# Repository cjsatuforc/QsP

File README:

3D Printer main driver board incorporating Atmel XMEGA. Inspired by RUMBA and other RepRap projects.

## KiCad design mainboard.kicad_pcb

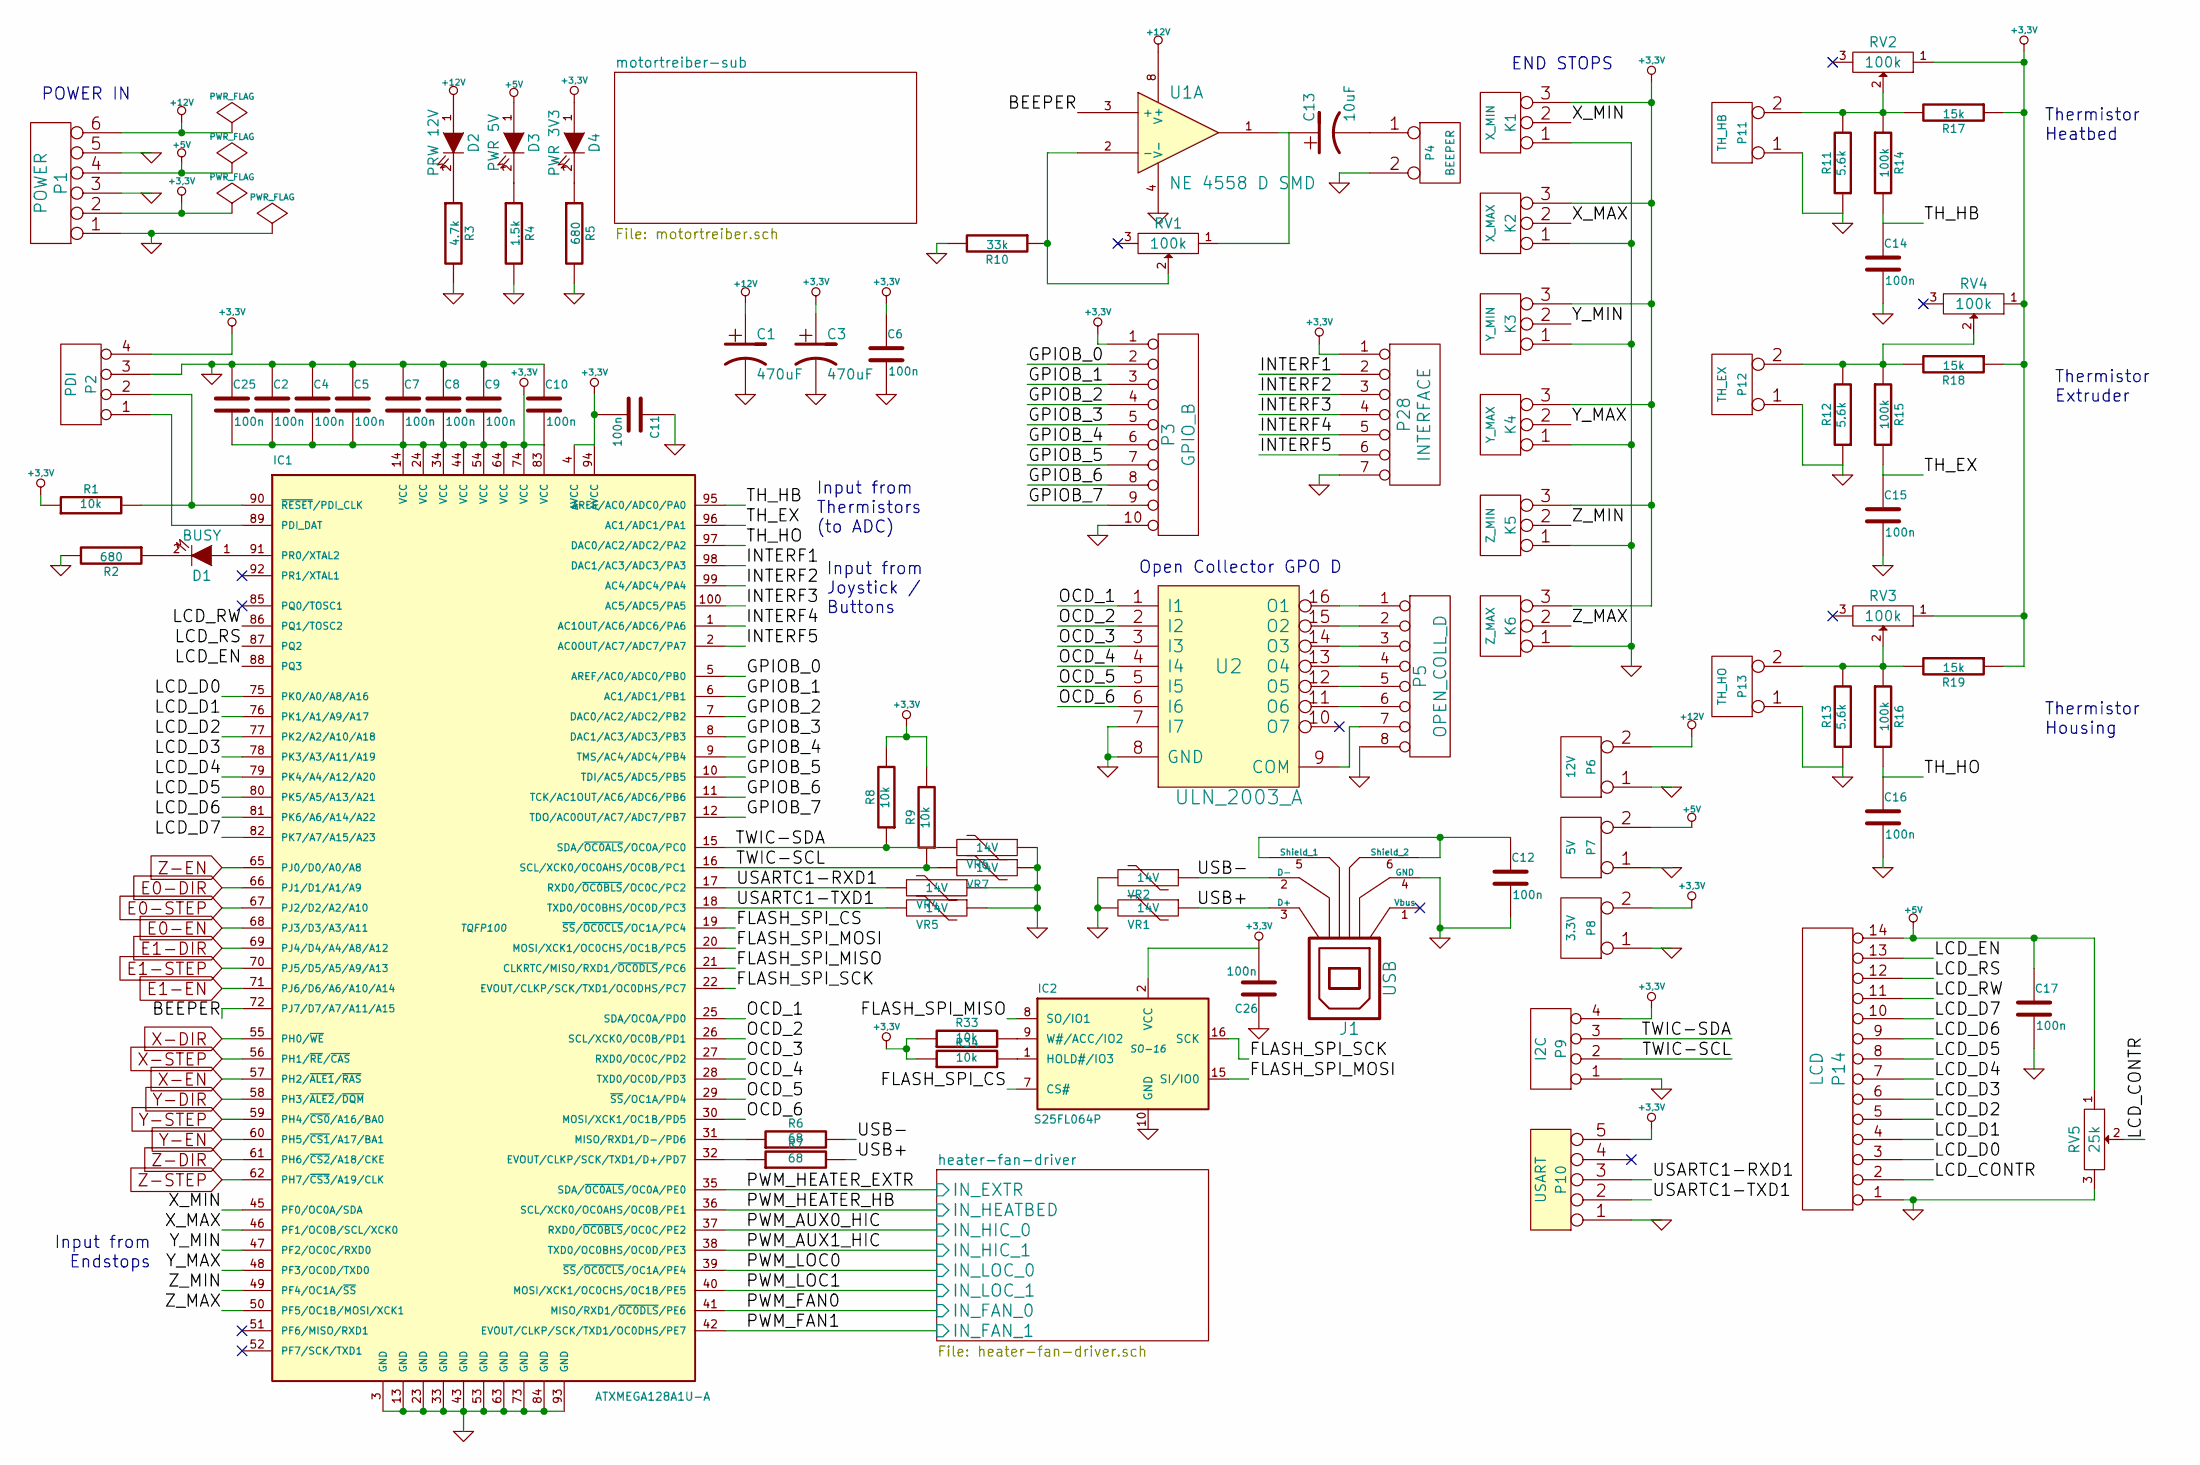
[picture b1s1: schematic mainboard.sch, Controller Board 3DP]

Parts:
C1, C3: 470uF
C2, C4, C5, C6, C7, C8, C9, C10, C11, C25, C26: 100n
C12, C14, C15, C16, C17: 100n
C13: 10uF
D1: BUSY
D2: PRW 12V
D3: PWR 5V
D4: PWR 3V3
IC1: ATXMEGA128A1U-A; TQFP100
IC2: S25FL064P; SO-16
J1: USB
K1: X_MIN
K2: X_MAX
K3: Y_MIN
K4: Y_MAX
K5: Z_MIN
K6: Z_MAX
P1: POWER
P2: PDI
P3: GPIO_B
P4: BEEPER
P5: OPEN_COLL_D
P6: 12V
P7: 5V
P8: 3.3V
P9: I2C
P10: USART
P11: TH_HB
P12: TH_EX
P13: TH_HO
P14: LCD
P28: INTERFACE
R1: 10k
R2, R5: 680
R3: 4.7k
R4: 1.5k
R6, R7: 68
R8, R9, R33, R34: 10k
R10: 33k
R11, R12, R13: 5.6k
R14, R15, R16: 100k
R17, R18, R19: 15k
RV1, RV2, RV3, RV4: 100k
RV5: 25k
U1: NE 4558 D SMD
U2: ULN_2003_A
VR1, VR2, VR4, VR5, VR6, VR7: 14V

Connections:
+3.3V: C2.2, C3.1, C4.2, C5.2, C6.1, C7.2, C8.2, C9.2, C10.2, C11.2, C25.2, C26.2, D4.1 (A), IC1.4 (AVCC), IC1.14 (VCC), IC1.24 (VCC), IC1.34 (VCC), IC1.44 (VCC), IC1.54 (VCC), IC1.64 (VCC), IC1.74 (VCC), IC1.83 (VCC), IC1.94 (AVCC), IC2.2 (VCC), K1.3, K2.3, K3.3, K4.3, K5.3, K6.3, P1.2, P2.4, P3.1, P8.2 (PM), P9.4, P10.5, P28.1, R1.1, R8.2, R9.2, R17.1, R18.1, R19.1, R33.1, R34.1, RV2.1, RV3.1, RV4.1; also elsewhere on the board
+5V: C17.1, D3.1 (A), P1.4, P7.2 (PM), P14.14, RV5.1
+12V: C1.1, D2.1 (A), P1.6, P6.2 (PM), U1.8 (V+); also elsewhere on the board
/BEEPER: IC1.72 (PJ7/D7/A7/A11/A15), U1.3 (+)
/FLASH_SPI_CS: IC1.19 (~SS~/~OC0CLS~/OC1A/PC4), IC2.7 (CS#)
/FLASH_SPI_MISO: IC1.21 (CLKRTC/MISO/RXD1/~OC0DLS~/PC6), IC2.8 (SO/IO1)
/FLASH_SPI_MOSI: IC1.20 (MOSI/XCK1/OC0CHS/OC1B/PC5), IC2.15 (SI/IO0)
/FLASH_SPI_SCK: IC1.22 (EVOUT/CLKP/SCK/TXD1/OC0DHS/PC7), IC2.16 (SCK)
/GPIOB_0: IC1.5 (AREF/AC0/ADC0/PB0), P3.2
/GPIOB_1: IC1.6 (AC1/ADC1/PB1), P3.3
/GPIOB_2: IC1.7 (DAC0/AC2/ADC2/PB2), P3.4
/GPIOB_3: IC1.8 (DAC1/AC3/ADC3/PB3), P3.5
/GPIOB_4: IC1.9 (TMS/AC4/ADC4/PB4), P3.6
/GPIOB_5: IC1.10 (TDI/AC5/ADC5/PB5), P3.7
/GPIOB_6: IC1.11 (TCK/AC1OUT/AC6/ADC6/PB6), P3.8
/GPIOB_7: IC1.12 (TDO/AC0OUT/AC7/ADC7/PB7), P3.9
/INTERF1: IC1.98 (DAC1/AC3/ADC3/PA3), P28.2
/INTERF2: IC1.99 (AC4/ADC4/PA4), P28.3
/INTERF3: IC1.100 (AC5/ADC5/PA5), P28.4
/INTERF4: IC1.1 (AC1OUT/AC6/ADC6/PA6), P28.5
/INTERF5: IC1.2 (AC0OUT/AC7/ADC7/PA7), P28.6
/LCD_CONTR: P14.2, RV5.2
/LCD_D0: IC1.75 (PK0/A0/A8/A16), P14.3
/LCD_D1: IC1.76 (PK1/A1/A9/A17), P14.4
/LCD_D2: IC1.77 (PK2/A2/A10/A18), P14.5
/LCD_D3: IC1.78 (PK3/A3/A11/A19), P14.6
/LCD_D4: IC1.79 (PK4/A4/A12/A20), P14.7
/LCD_D5: IC1.80 (PK5/A5/A13/A21), P14.8
/LCD_D6: IC1.81 (PK6/A6/A14/A22), P14.9
/LCD_D7: IC1.82 (PK7/A7/A15/A23), P14.10
/LCD_EN: IC1.88 (PQ3), P14.13
/LCD_RS: IC1.87 (PQ2), P14.12
/LCD_RW: IC1.86 (PQ1/TOSC2), P14.11
/OCD_1: IC1.25 (SDA/OC0A/PD0), U2.1 (I1)
/OCD_2: IC1.26 (SCL/XCK0/OC0B/PD1), U2.2 (I2)
/OCD_3: IC1.27 (RXD0/OC0C/PD2), U2.3 (I3)
/OCD_4: IC1.28 (TXD0/OC0D/PD3), U2.4 (I4)
/OCD_5: IC1.29 (~SS~/OC1A/PD4), U2.5 (I5)
/OCD_6: IC1.30 (MOSI/XCK1/OC1B/PD5), U2.6 (I6)
/TH_EX: C15.1, IC1.96 (AC1/ADC1/PA1), R15.2
/TH_HB: C14.1, IC1.95 (AREF/AC0/ADC0/PA0), R14.2
/TH_HO: C16.1, IC1.97 (DAC0/AC2/ADC2/PA2), R16.2
/TWIC-SCL: IC1.16 (SCL/XCK0/OC0AHS/OC0B/PC1), P9.2, R9.1, VR7.2
/TWIC-SDA: IC1.15 (SDA/~OC0ALS~/OC0A/PC0), P9.3, R8.1, VR6.2
/USARTC1-RXD1: IC1.17 (RXD0/~OC0BLS~/OC0C/PC2), P10.3, VR4.2
/USARTC1-TXD1: IC1.18 (TXD0/OC0BHS/OC0D/PC3), P10.2, VR5.2
/USB+: J1.3 (D+), R7.2, VR1.1
/USB-: J1.2 (D-), R6.2, VR2.1
/X_MAX: IC1.46 (PF1/OC0B/SCL/XCK0), K2.2 (PM)
/X_MIN: IC1.45 (PF0/OC0A/SDA), K1.2 (PM)
/Y_MAX: IC1.48 (PF3/OC0D/TXD0), K4.2 (PM)
/Y_MIN: IC1.47 (PF2/OC0C/RXD0), K3.2 (PM)
/Z_MAX: IC1.50 (PF5/OC1B/MOSI/XCK1), K6.2 (PM)
/Z_MIN: IC1.49 (PF4/OC1A/~SS~), K5.2 (PM)
/heater-fan-driver/IN_EXTR: IC1.35 (SDA/~OC0ALS~/OC0A/PE0); also elsewhere on the board
/heater-fan-driver/IN_FAN_0: IC1.41 (MISO/RXD1/~OC0DLS~/PE6); also elsewhere on the board
/heater-fan-driver/IN_FAN_1: IC1.42 (EVOUT/CLKP/SCK/TXD1/OC0DHS/PE7); also elsewhere on the board
/heater-fan-driver/IN_HEATBED: IC1.36 (SCL/XCK0/OC0AHS/OC0B/PE1); also elsewhere on the board
/heater-fan-driver/IN_HIC_0: IC1.37 (RXD0/~OC0BLS~/OC0C/PE2); also elsewhere on the board
/heater-fan-driver/IN_HIC_1: IC1.38 (TXD0/OC0BHS/OC0D/PE3); also elsewhere on the board
/heater-fan-driver/IN_LOC_0: IC1.39 (~SS~/~OC0CLS~/OC1A/PE4); also elsewhere on the board
/heater-fan-driver/IN_LOC_1: IC1.40 (MOSI/XCK1/OC0CHS/OC1B/PE5); also elsewhere on the board
E0-DIR: IC1.66 (PJ1/D1/A1/A9); also elsewhere on the board
E0-EN: IC1.68 (PJ3/D3/A3/A11); also elsewhere on the board
E0-STEP: IC1.67 (PJ2/D2/A2/A10); also elsewhere on the board
E1-DIR: IC1.69 (PJ4/D4/A4/A8/A12); also elsewhere on the board
E1-EN: IC1.71 (PJ6/D6/A6/A10/A14); also elsewhere on the board
E1-STEP: IC1.70 (PJ5/D5/A5/A9/A13); also elsewhere on the board
GND: C1.2, C2.1, C3.2, C4.1, C5.1, C6.2, C7.1, C8.1, C9.1, C10.1, C11.1, C12.2, C14.2, C15.2, C16.2, C17.2, C25.1, C26.1, IC1.3 (GND), IC1.13 (GND), IC1.23 (GND), IC1.33 (GND), IC1.43 (GND), IC1.53 (GND), IC1.63 (GND), IC1.73 (GND), IC1.84 (GND), IC1.93 (GND), IC2.10 (GND), J1.4 (GND), K1.1, K2.1, K3.1, K4.1, K5.1, K6.1, P1.1, P1.3, P1.5, P2.3, P3.10, P4.2 (PM), P5.8, P6.1, P7.1, P8.1, P9.1, P10.1, P11.1, P12.1, P13.1, P14.1, P28.7, R2.2, R3.2, R4.2, R5.2, R10.2, R11.1, R12.1, R13.1, RV5.3, U1.4 (V-), U2.7 (I7), U2.8 (GND), VR1.2, VR2.2, VR4.1, VR5.1, VR6.1, VR7.1; also elsewhere on the board
unnamed: C12.1, J1.5 (Shield_1), J1.6 (Shield_2)
unnamed: C13.1, RV1.1, U1.1
unnamed: C13.2, P4.1
unnamed: D1.1 (A), IC1.91 (PR0/XTAL2)
unnamed: D1.2 (K), R2.1
unnamed: D2.2 (K), R3.1
unnamed: D3.2 (K), R4.1
unnamed: D4.2 (K), R5.1
unnamed: IC1.31 (MISO/RXD1/D-/PD6), R6.1
unnamed: IC1.32 (EVOUT/CLKP/SCK/TXD1/D+/PD7), R7.1
unnamed: IC1.89 (PDI_DAT), P2.1
unnamed: IC1.90 (~RESET~/PDI_CLK), P2.2, R1.2
unnamed: IC2.1 (HOLD#/IO3), R34.2
unnamed: IC2.9 (W#/ACC/IO2), R33.2
unnamed: P5.1, U2.16 (O1)
unnamed: P5.2, U2.15 (O2)
unnamed: P5.3, U2.14 (O3)
unnamed: P5.4, U2.13 (O4)
unnamed: P5.5, U2.12 (O5)
unnamed: P5.6, U2.11 (O6)
unnamed: P5.7, U2.9 (COM)
unnamed: P11.2 (PM), R11.2, R14.1, R17.2, RV2.2
unnamed: P12.2 (PM), R12.2, R15.1, R18.2, RV4.2
unnamed: P13.2 (PM), R13.2, R16.1, R19.2, RV3.2
unnamed: R10.1, RV1.2, U1.2 (-)
X-DIR: IC1.55 (PH0/~WE); also elsewhere on the board
X-EN: IC1.57 (PH2/~ALE1~/~RAS~); also elsewhere on the board
X-STEP: IC1.56 (PH1/~RE~/~CAS~); also elsewhere on the board
Y-DIR: IC1.58 (PH3/~ALE2~/~DQM~); also elsewhere on the board
Y-EN: IC1.60 (PH5/~CS1~/A17/BA1); also elsewhere on the board
Y-STEP: IC1.59 (PH4/~CS0~/A16/BA0); also elsewhere on the board
Z-DIR: IC1.61 (PH6/~CS2~/A18/CKE); also elsewhere on the board
Z-EN: IC1.65 (PJ0/D0/A0/A8); also elsewhere on the board
Z-STEP: IC1.62 (PH7/~CS3~/A19/CLK); also elsewhere on the board

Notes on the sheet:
POWER IN
END STOPS
Thermistor Heatbed
Thermistor Extruder
Thermistor Housing
Input from Endstops
Input from Thermistors (to ADC)
Input from Joystick / Buttons
Open Collector GPO D

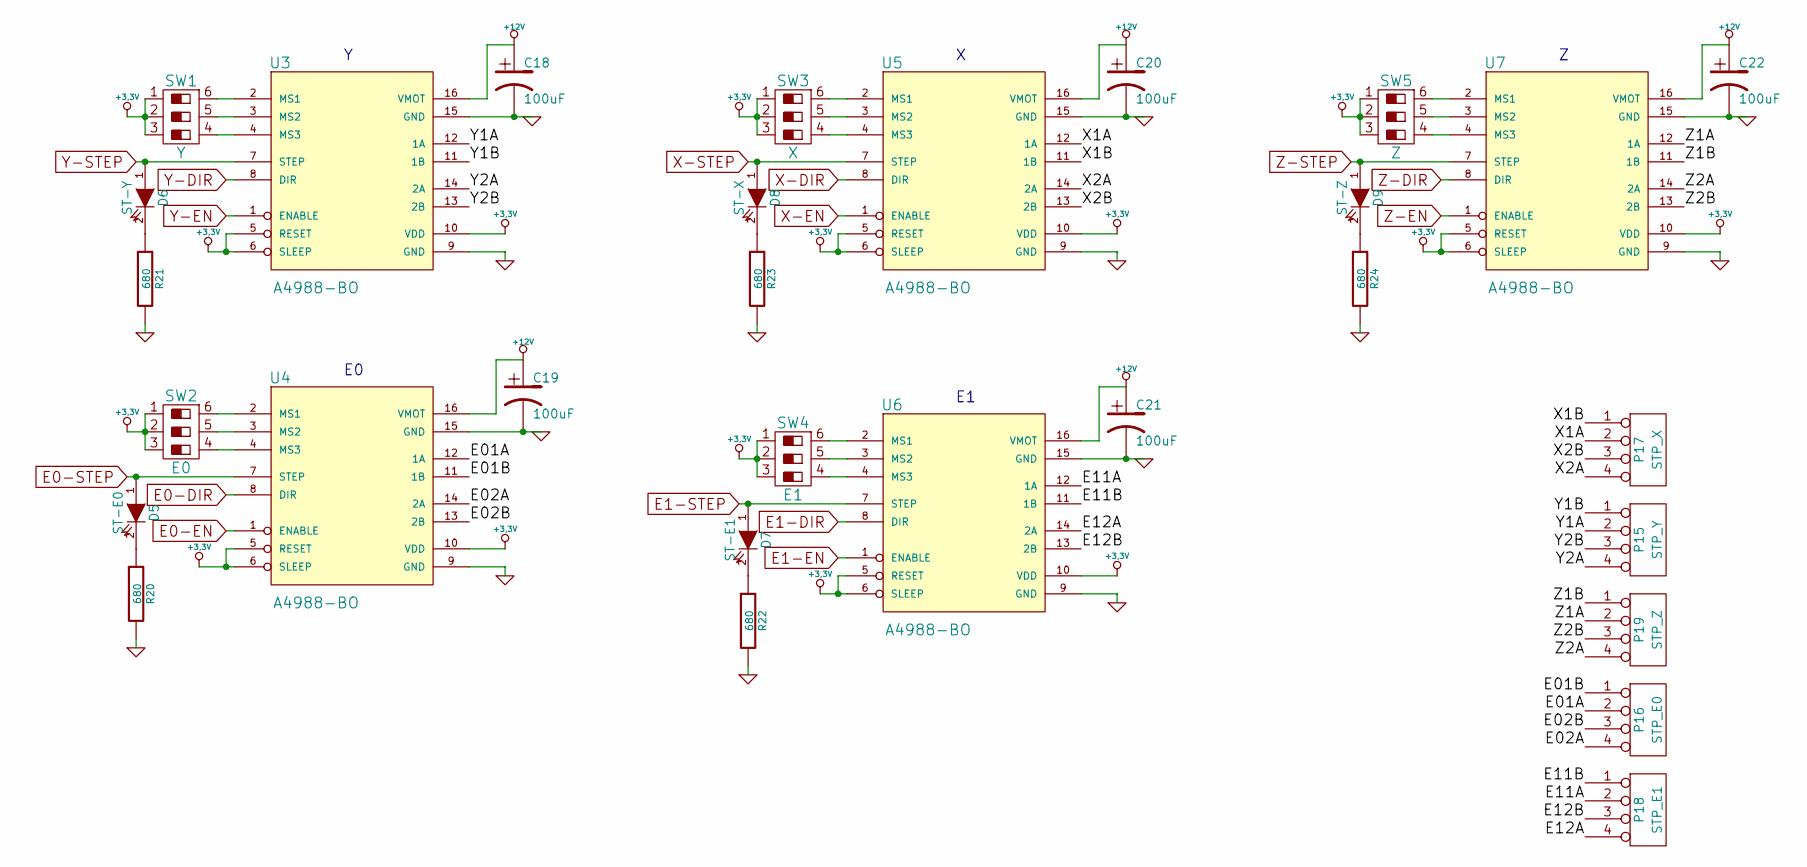
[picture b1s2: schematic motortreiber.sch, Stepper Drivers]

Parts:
C18, C19, C20, C21, C22: 100uF
D5: ST-E0
D6: ST-Y
D7: ST-E1
D8: ST-X
D9: ST-Z
P15: STP_Y
P16: STP_E0
P17: STP_X
P18: STP_E1
P19: STP_Z
R20, R21, R22, R23, R24: 680
SW1: Y
SW2: E0
SW3: X
SW4: E1
SW5: Z
U3, U4, U5, U6, U7: A4988-BO

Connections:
+3.3V: SW1.1, SW1.2, SW1.3, SW2.1, SW2.2, SW2.3, SW3.1, SW3.2, SW3.3, SW4.1, SW4.2, SW4.3, SW5.1, SW5.2, SW5.3, U3.5 (RESET), U3.6 (SLEEP), U3.10 (VDD), U4.5 (RESET), U4.6 (SLEEP), U4.10 (VDD), U5.5 (RESET), U5.6 (SLEEP), U5.10 (VDD), U6.5 (RESET), U6.6 (SLEEP), U6.10 (VDD), U7.5 (RESET), U7.6 (SLEEP), U7.10 (VDD); also elsewhere on the board
+12V: C18.1, C19.1, C20.1, C21.1, C22.1, U3.16 (VMOT), U4.16 (VMOT), U5.16 (VMOT), U6.16 (VMOT), U7.16 (VMOT); also elsewhere on the board
/motortreiber-sub/E01A: P16.2, U4.12 (1A)
/motortreiber-sub/E01B: P16.1, U4.11 (1B)
/motortreiber-sub/E02A: P16.4, U4.14 (2A)
/motortreiber-sub/E02B: P16.3, U4.13 (2B)
/motortreiber-sub/E11A: P18.2, U6.12 (1A)
/motortreiber-sub/E11B: P18.1, U6.11 (1B)
/motortreiber-sub/E12A: P18.4, U6.14 (2A)
/motortreiber-sub/E12B: P18.3, U6.13 (2B)
/motortreiber-sub/X1A: P17.2, U5.12 (1A)
/motortreiber-sub/X1B: P17.1, U5.11 (1B)
/motortreiber-sub/X2A: P17.4, U5.14 (2A)
/motortreiber-sub/X2B: P17.3, U5.13 (2B)
/motortreiber-sub/Y1A: P15.2, U3.12 (1A)
/motortreiber-sub/Y1B: P15.1, U3.11 (1B)
/motortreiber-sub/Y2A: P15.4, U3.14 (2A)
/motortreiber-sub/Y2B: P15.3, U3.13 (2B)
/motortreiber-sub/Z1A: P19.2, U7.12 (1A)
/motortreiber-sub/Z1B: P19.1, U7.11 (1B)
/motortreiber-sub/Z2A: P19.4, U7.14 (2A)
/motortreiber-sub/Z2B: P19.3, U7.13 (2B)
E0-DIR: U4.8 (DIR); also elsewhere on the board
E0-EN: U4.1 (ENABLE); also elsewhere on the board
E0-STEP: D5.1 (A), U4.7 (STEP); also elsewhere on the board
E1-DIR: U6.8 (DIR); also elsewhere on the board
E1-EN: U6.1 (ENABLE); also elsewhere on the board
E1-STEP: D7.1 (A), U6.7 (STEP); also elsewhere on the board
GND: C18.2, C19.2, C20.2, C21.2, C22.2, R20.2, R21.2, R22.2, R23.2, R24.2, U3.9 (GND), U3.15 (GND), U4.9 (GND), U4.15 (GND), U5.9 (GND), U5.15 (GND), U6.9 (GND), U6.15 (GND), U7.9 (GND), U7.15 (GND); also elsewhere on the board
unnamed: D5.2 (K), R20.1
unnamed: D6.2 (K), R21.1
unnamed: D7.2 (K), R22.1
unnamed: D8.2 (K), R23.1
unnamed: D9.2 (K), R24.1
unnamed: SW1.4, U3.4 (MS3)
unnamed: SW1.5, U3.3 (MS2)
unnamed: SW1.6, U3.2 (MS1)
unnamed: SW2.4, U4.4 (MS3)
unnamed: SW2.5, U4.3 (MS2)
unnamed: SW2.6, U4.2 (MS1)
unnamed: SW3.4, U5.4 (MS3)
unnamed: SW3.5, U5.3 (MS2)
unnamed: SW3.6, U5.2 (MS1)
unnamed: SW4.4, U6.4 (MS3)
unnamed: SW4.5, U6.3 (MS2)
unnamed: SW4.6, U6.2 (MS1)
unnamed: SW5.4, U7.4 (MS3)
unnamed: SW5.5, U7.3 (MS2)
unnamed: SW5.6, U7.2 (MS1)
X-DIR: U5.8 (DIR); also elsewhere on the board
X-EN: U5.1 (ENABLE); also elsewhere on the board
X-STEP: D8.1 (A), U5.7 (STEP); also elsewhere on the board
Y-DIR: U3.8 (DIR); also elsewhere on the board
Y-EN: U3.1 (ENABLE); also elsewhere on the board
Y-STEP: D6.1 (A), U3.7 (STEP); also elsewhere on the board
Z-DIR: U7.8 (DIR); also elsewhere on the board
Z-EN: U7.1 (ENABLE); also elsewhere on the board
Z-STEP: D9.1 (A), U7.7 (STEP); also elsewhere on the board

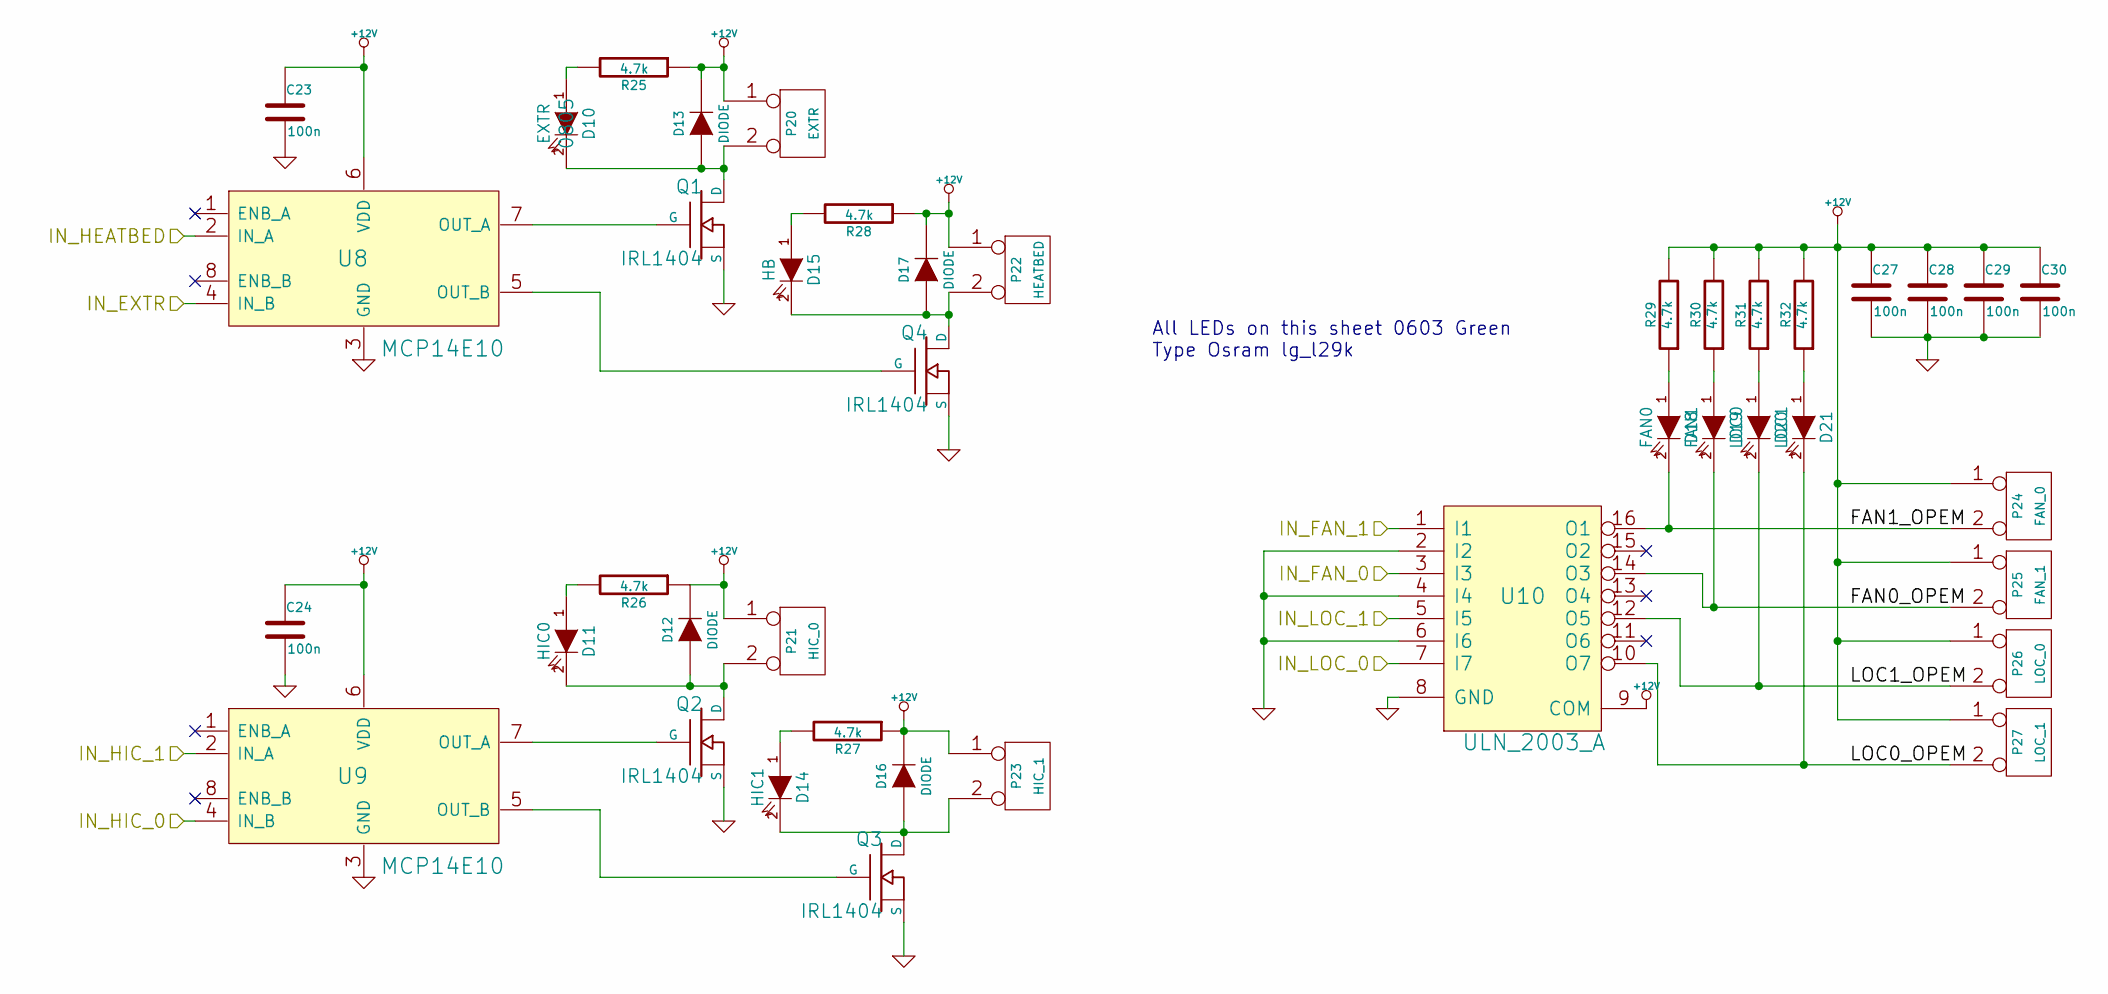
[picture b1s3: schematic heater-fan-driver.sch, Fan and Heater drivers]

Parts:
C23, C24, C27, C28, C29, C30: 100n
D10: EXTR; 0805
D11: HIC0
D12, D13, D16, D17: DIODE
D14: HIC1
D15: HB
D18: FAN0
D19: FAN1
D20: LOC0
D21: LOC1
P20: EXTR
P21: HIC_0
P22: HEATBED
P23: HIC_1
P24: FAN_0
P25: FAN_1
P26: LOC_0
P27: LOC_1
Q1, Q2, Q3, Q4: IRL1404
R25, R26, R27, R28, R29, R30, R31, R32: 4.7k
U8, U9: MCP14E10
U10: ULN_2003_A

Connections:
+12V: C23.1, C24.1, C27.1, C28.1, C29.1, C30.1, D12.2 (K), D13.2 (K), D16.2 (K), D17.2 (K), P20.1, P21.1, P22.1, P23.1, P24.1, P25.1, P26.1, P27.1, R25.1, R26.1, R27.1, R28.1, R29.2, R30.2, R31.2, R32.2, U8.6 (VDD), U9.6 (VDD), U10.9 (COM); also elsewhere on the board
/heater-fan-driver/FAN0_OPEM: D19.2 (K), P25.2 (PM), U10.14 (O3)
/heater-fan-driver/FAN1_OPEM: D18.2 (K), P24.2 (PM), U10.16 (O1)
/heater-fan-driver/IN_EXTR: U8.4 (IN_B); also elsewhere on the board
/heater-fan-driver/IN_FAN_0: U10.3 (I3); also elsewhere on the board
/heater-fan-driver/IN_FAN_1: U10.1 (I1); also elsewhere on the board
/heater-fan-driver/IN_HEATBED: U8.2 (IN_A); also elsewhere on the board
/heater-fan-driver/IN_HIC_0: U9.4 (IN_B); also elsewhere on the board
/heater-fan-driver/IN_HIC_1: U9.2 (IN_A); also elsewhere on the board
/heater-fan-driver/IN_LOC_0: U10.7 (I7); also elsewhere on the board
/heater-fan-driver/IN_LOC_1: U10.5 (I5); also elsewhere on the board
/heater-fan-driver/LOC0_OPEM: D21.2 (K), P27.2 (PM), U10.10 (O7)
/heater-fan-driver/LOC1_OPEM: D20.2 (K), P26.2 (PM), U10.12 (O5)
GND: C23.2, C24.2, C27.2, C28.2, C29.2, C30.2, Q1.S, Q2.S, Q3.S, Q4.S, U8.3 (GND), U9.3 (GND), U10.2 (I2), U10.4 (I4), U10.6 (I6), U10.8 (GND); also elsewhere on the board
unnamed: D10.1 (A), R25.2
unnamed: D10.2 (K), D13.1 (A), P20.2 (PM), Q1.D
unnamed: D11.1 (A), R26.2
unnamed: D11.2 (K), D12.1 (A), P21.2 (PM), Q2.D
unnamed: D14.1 (A), R27.2
unnamed: D14.2 (K), D16.1 (A), P23.2 (PM), Q3.D
unnamed: D15.1 (A), R28.2
unnamed: D15.2 (K), D17.1 (A), P22.2 (PM), Q4.D
unnamed: D18.1 (A), R29.1
unnamed: D19.1 (A), R30.1
unnamed: D20.1 (A), R31.1
unnamed: D21.1 (A), R32.1
unnamed: Q1.G, U8.7 (OUT_A)
unnamed: Q2.G, U9.7 (OUT_A)
unnamed: Q3.G, U9.5 (OUT_B)
unnamed: Q4.G, U8.5 (OUT_B)

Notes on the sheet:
All LEDs on this sheet 0603 Green Type Osram lg_l29k

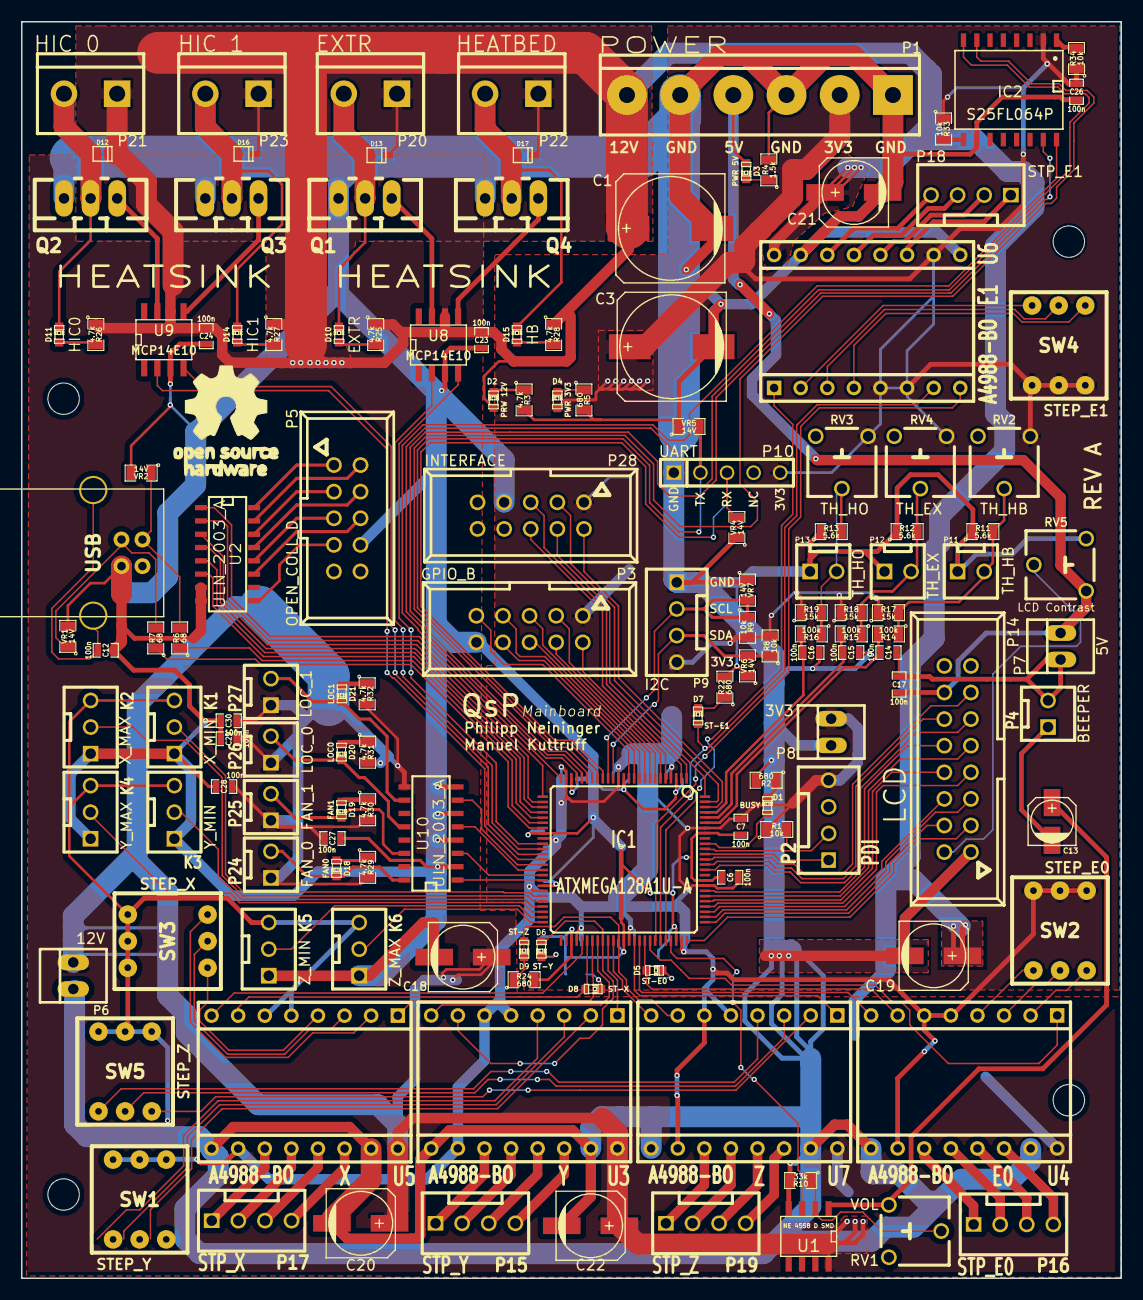
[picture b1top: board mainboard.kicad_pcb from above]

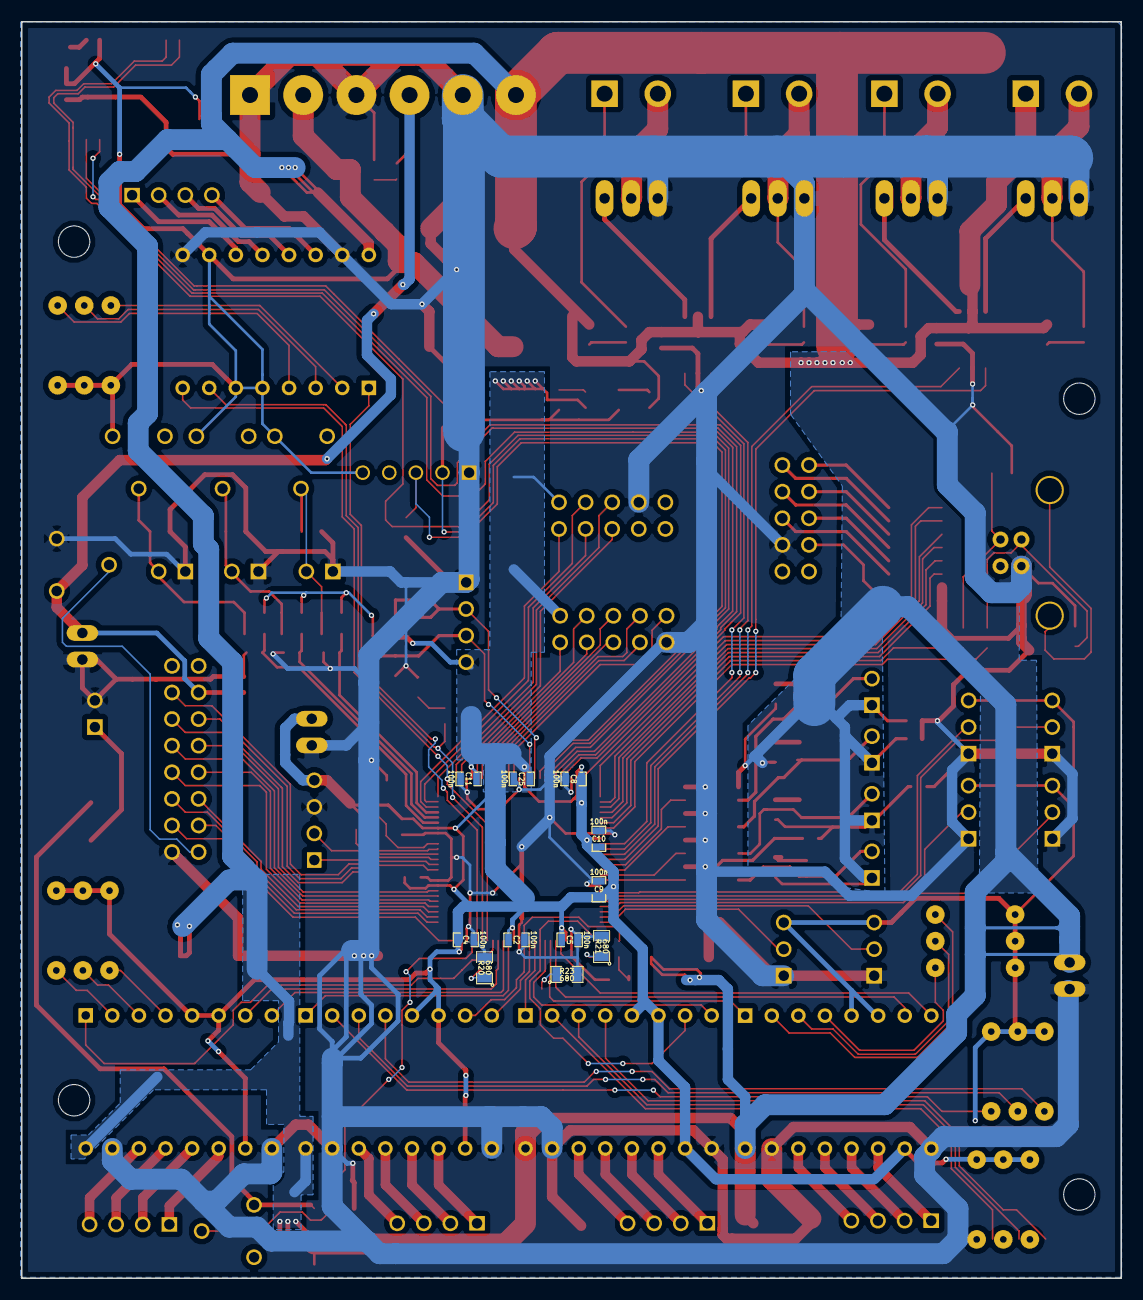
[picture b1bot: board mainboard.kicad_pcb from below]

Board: 2 copper layers, 105.0 x 120.0 mm, 152 parts (11 on the bottom side), 163 nets.

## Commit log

2014-03-26 Added notes/toDo file, swapped xMEGA for a model from kicad standard library
2014-03-26 Added a bunch of new labels to the microcontroller
2014-03-26 removed 1 stepper motor driver (-> to have enough ports left for the LCD), added low pass filters to thermistor inputs
2014-03-27 Added LCD connector (pin assignment for connector tbd). Added 555 timer circuit for beeper (400Hz)
2014-03-28 Removed 555-Timer-Circuit. Added Opamp to drive beeper.
2014-03-29 Changed OpAmp to NE 4558D SMD
2014-03-29 Calculated resistor values for thermistor and changed them in the schematic
2014-03-30 Added Pot to trim ADC input for thermistors
2014-04-15 Changed UC to ATxmega128A1U (TQFP100) which has more pins.
2014-04-15 Added USART and I2C connectors, reworked pin mappings for new UC
2014-04-16 Added schematic for pwm-drivers. Added ULN 2003 as low current driver.
2014-04-17 Added 12V-connector. Changed LCD connector to 14-pin (including d0-d7 now)
2014-04-17 Added signal LEDs to hi-current and lo-current drivers, updated BOM
2014-04-17 Added Open Collector connector for future expansion
2014-04-17 Added potentiometer to make beeper volume adjustable
2014-04-18 Added protection diodes for heater drivers Added pcb file (empty yet)
2014-04-18 Added footprint for a4988 breakout-board
2014-04-18 LICENSE and README for publication
2014-04-18 Input protection for USB, I2C and USART
2014-04-19 Added some LEDs for a better overview what the board is doing when operating; Generated netlist and started to associate footprints
2014-04-19 Added pullup resistors to I2C interface and protection resistors for USB interface
2014-04-19 Added decoupling cap for display supply; Associated most footprints.
2014-04-20 Finished footprint association; added footprint for potentiometer
2014-04-21 Added status LEDs for 5V and 12V power
2014-04-21 Added missing interface connector; reworked schematic. Started to layout PCB
2014-04-21 Reworked schematic
2014-04-22 * Changed connectors to PSK type - this prevents plugging the steppers in the wrong way * Changed stepping increment jumpers to DIP-switches - easier setting
2014-04-22 * Added PSK-2 connector to library * Changed Low-Current outputs (FANs etc) to PSK-2 connectors
2014-04-22 Added footprint for SOD323 diode package and replaced former MELF-package
2014-04-22 Changed USART connector to show the respective net each pin is connected to
2014-04-23 * Removed numerous errors, schematic now passes ERC test. * Arranged footprints on PCB to prepare for routing
2014-04-24 Added decoupling caps for MOSFET drivers
2014-04-26 * Changed order of stepper connections to UC to ease PCB routing * Arranged all items in 12x12cm space, ready to route(?)
2014-05-02 * Schematic: Added decoupling cap for XMega * Schematic: Changed connector pin assignment for easier routing * Board: Changed arrangement of some components * Board: Routed all signal nets. To Do: Po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
2014-05-03 Router parts of the power layer
2014-05-06 Added board outline
2014-05-13 * Added 64Mbit Flash Memory to schematic * Finalized power routing
2014-05-13 Changed ground plane clearance
2014-05-14 * top layer: added filled areas, other optimizations * changed drills, removed bottom solder mask from some through-hole components to make them solderable * added OSHW logo and moved some labels to 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
2014-08-16 * Added goals for REV B * More room for mounting hole (bottom left)
